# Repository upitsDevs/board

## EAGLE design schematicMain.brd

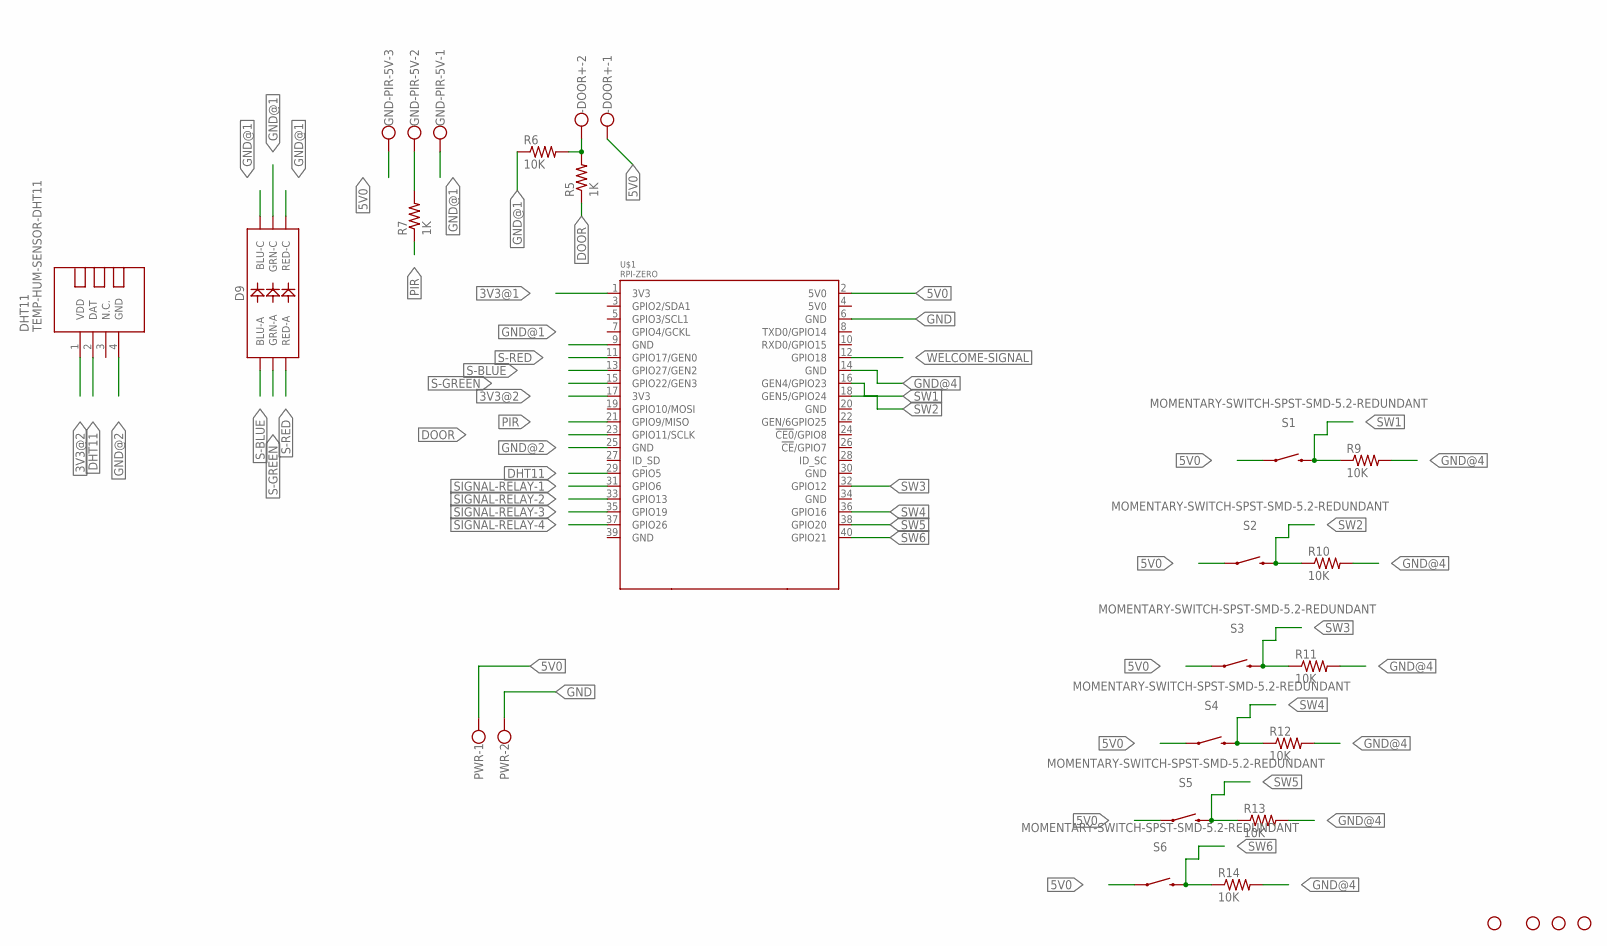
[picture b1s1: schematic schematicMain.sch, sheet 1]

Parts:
-DOOR+: W237-102
D9: RGB; LED-TRICOLOR-5050
DHT11: TEMP-HUM-SENSOR-DHT11
GND-PIR-5V: W237-103
H1, H2, H3, H4: STAND-OFFTIGHT; STAND-OFF-TIGHT
PWR: W237-102
R5, R7: 1K; M1206
R6, R9, R10, R11, R12, R13, R14: 10K; M1206
S1, S2, S3, S4, S5, S6: MOMENTARY-SWITCH-SPST-SMD-5.2-REDUNDANT; TACTILE_SWITCH_SMD_5.2MM
U$1: RPI-ZERO; RASPBERRYPI_BASTELSTUBE_V13_RASPI_BOARD_B+_FULL

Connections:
3V3@1: U$1.1 (3V3)
3V3@2: DHT11.1 (VDD), U$1.17 (3V3)
5V0: -DOOR+.1, GND-PIR-5V.3, PWR.1, S1.1, S1.2 (1), S2.1, S2.2 (1), S3.1, S3.2 (1), S4.1, S4.2 (1), S5.1, S5.2 (1), S6.1, S6.2 (1), U$1.2 (5V0); also elsewhere on the board
DHT11: DHT11.2 (DAT), U$1.29 (GPIO5)
DOOR: R5.1, U$1.23 (GPIO11/SCLK)
GND: PWR.2, U$1.6 (GND); also elsewhere on the board
GND@1: D9.4 (BLU-C), D9.5 (RED-C), D9.6 (GRN-C), GND-PIR-5V.1, R6.1, U$1.9 (GND)
GND@2: DHT11.4 (GND), U$1.25 (GND)
GND@4: R9.2, R10.2, R11.2, R12.2, R13.2, R14.2, U$1.14 (GND)
unnamed: GND-PIR-5V.2, R7.2
unnamed: -DOOR+.2, R5.2, R6.2
PIR: R7.1, U$1.21 (GPIO9/MISO)
S-BLUE: D9.3 (BLU-A), U$1.13 (GPIO27/GEN2)
S-GREEN: D9.1 (GRN-A), U$1.15 (GPIO22/GEN3)
S-RED: D9.2 (RED-A), U$1.11 (GPIO17/GEN0)
SIGNAL-RELAY-1: U$1.31 (GPIO6); also elsewhere on the board
SIGNAL-RELAY-2: U$1.33 (GPIO13); also elsewhere on the board
SIGNAL-RELAY-3: U$1.35 (GPIO19); also elsewhere on the board
SIGNAL-RELAY-4: U$1.37 (GPIO26); also elsewhere on the board
SW1: R9.1, S1.3 (2), S1.4 (2), U$1.16 (GEN4/GPIO23)
SW2: R10.1, S2.3 (2), S2.4 (2), U$1.18 (GEN5/GPIO24)
SW3: R11.1, S3.3 (2), S3.4 (2), U$1.32 (GPIO12)
SW4: R12.1, S4.3 (2), S4.4 (2), U$1.36 (GPIO16)
SW5: R13.1, S5.3 (2), S5.4 (2), U$1.38 (GPIO20)
SW6: R14.1, S6.3 (2), S6.4 (2), U$1.40 (GPIO21)
WELCOME-SIGNAL: U$1.12 (GPIO18); also elsewhere on the board

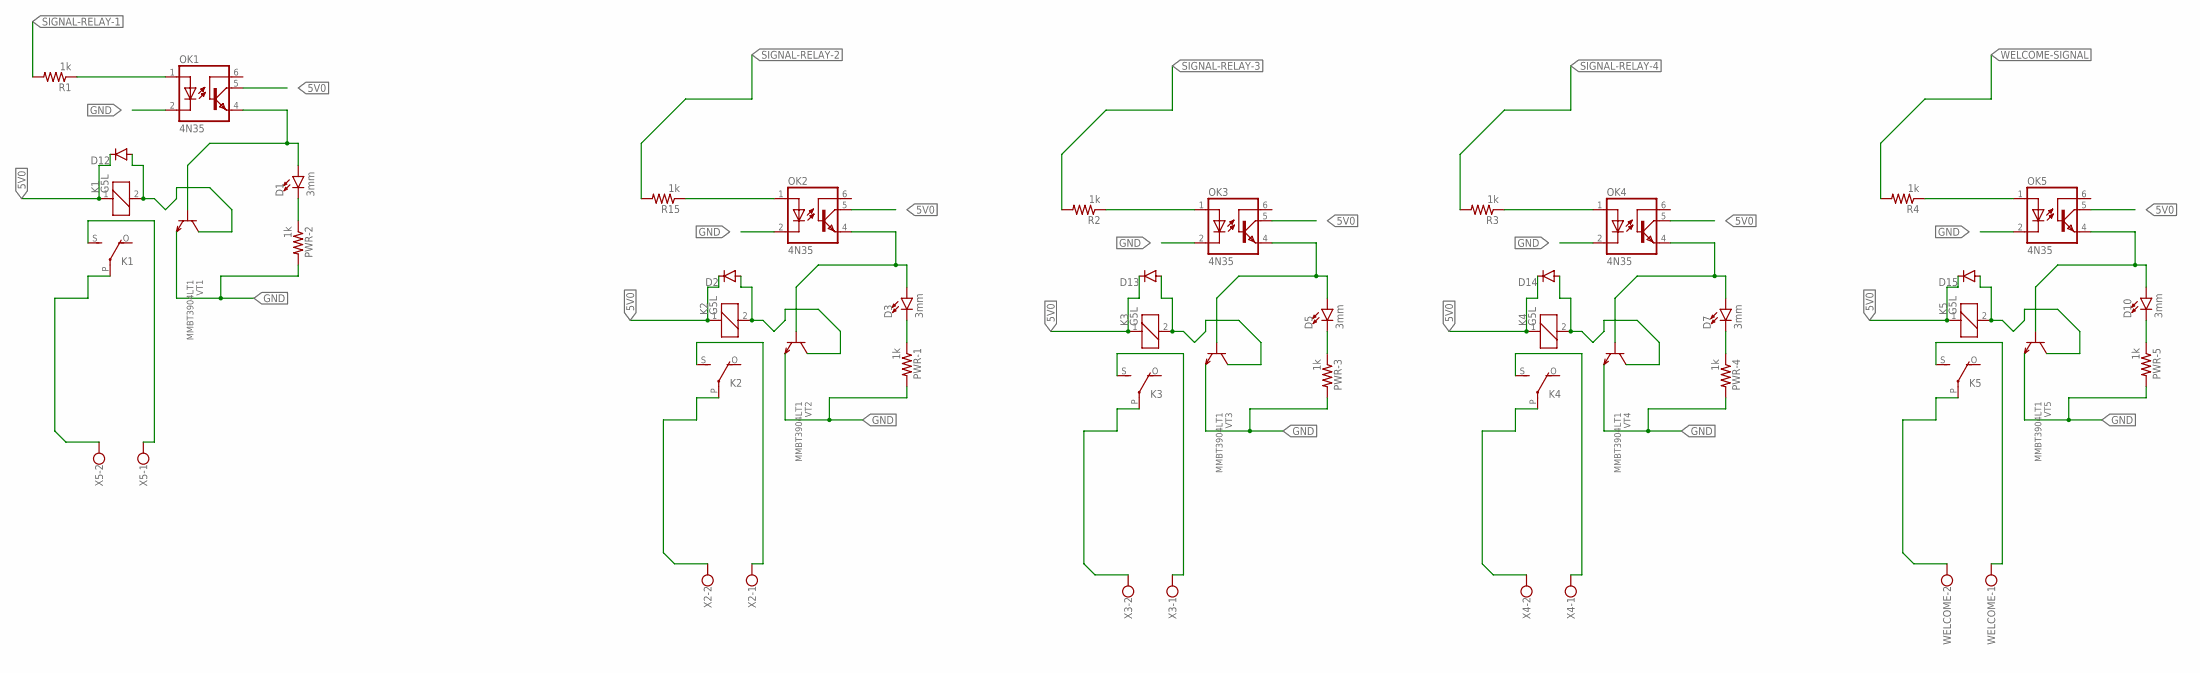
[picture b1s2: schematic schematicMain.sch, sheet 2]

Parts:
D1, D3, D5, D7, D10: 3mm; FKIT-LED-1206
D2, D12, D13, D14, D15: DIODE-SOD80C; SOD80C
K1, K2, K3, K4, K5: G5L; G5LE
OK1, OK2, OK3, OK4, OK5: 4N35; DIL06
PWR-1, PWR-2, PWR-3, PWR-4, PWR-5: 1k; M1206
R1, R2, R3, R4, R15: 1k; M1206
VT1, VT2, VT3, VT4, VT5: MMBT3904LT1; SOT23-BEC
WELCOME: W237-102
X2, X3, X4, X5: W237-102

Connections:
5V0: D2.C, D12.C, D13.C, D14.C, D15.C, K1.1, K2.1, K3.1, K4.1, K5.1, OK1.5 (COL), OK2.5 (COL), OK3.5 (COL), OK4.5 (COL), OK5.5 (COL); also elsewhere on the board
GND: OK1.2 (C), OK2.2 (C), OK3.2 (C), OK4.2 (C), OK5.2 (C), PWR-1.2, PWR-2.2, PWR-3.2, PWR-4.2, PWR-5.2, VT1.E, VT2.E, VT3.E, VT4.E, VT5.E; also elsewhere on the board
unnamed: K1.P, X5.2
unnamed: K1.S, X5.1
unnamed: K2.P, X2.2
unnamed: D1.A, OK1.4 (EMI), VT1.B
unnamed: D12.A, K1.2, VT1.C
unnamed: K5.P, WELCOME.2
unnamed: OK1.1 (A), R1.1
unnamed: K2.S, X2.1
unnamed: K5.S, WELCOME.1
unnamed: OK2.1 (A), R15.1
unnamed: D2.A, K2.2, VT2.C
unnamed: K3.P, X3.2
unnamed: K3.S, X3.1
unnamed: OK3.1 (A), R2.1
unnamed: OK5.1 (A), R4.1
unnamed: D13.A, K3.2, VT3.C
unnamed: D5.A, OK3.4 (EMI), VT3.B
unnamed: D5.C, PWR-3.1
unnamed: D15.A, K5.2, VT5.C
unnamed: K4.P, X4.2
unnamed: K4.S, X4.1
unnamed: D10.A, OK5.4 (EMI), VT5.B
unnamed: OK4.1 (A), R3.1
unnamed: D14.A, K4.2, VT4.C
unnamed: D7.A, OK4.4 (EMI), VT4.B
unnamed: D3.A, OK2.4 (EMI), VT2.B
unnamed: D1.C, PWR-2.1
unnamed: D3.C, PWR-1.1
unnamed: D7.C, PWR-4.1
unnamed: D10.C, PWR-5.1
SIGNAL-RELAY-1: R1.2; also elsewhere on the board
SIGNAL-RELAY-2: R15.2; also elsewhere on the board
SIGNAL-RELAY-3: R2.2; also elsewhere on the board
SIGNAL-RELAY-4: R3.2; also elsewhere on the board
WELCOME-SIGNAL: R4.2; also elsewhere on the board

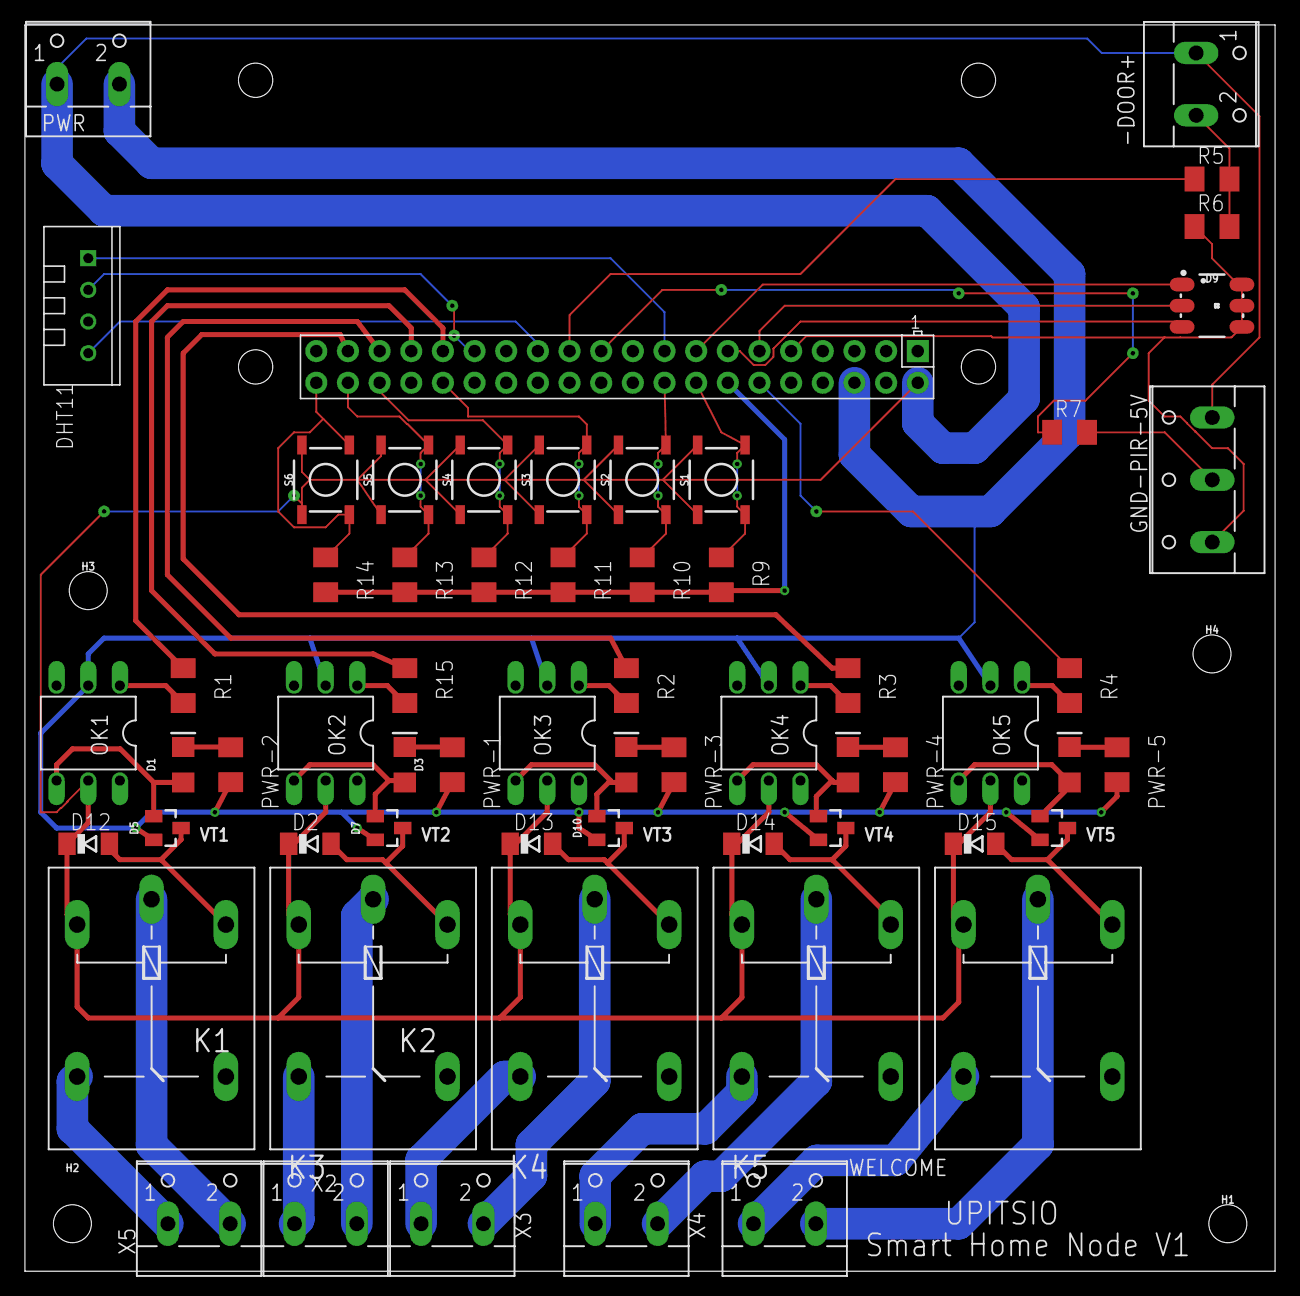
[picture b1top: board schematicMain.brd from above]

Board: 2 copper layers, 100.3 x 100.0 mm, 65 parts (0 on the bottom side), 55 nets.

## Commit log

2018-11-21 initial version
2018-11-21 Read me
2018-11-21 Updated Relay modules
2018-11-23 update 23-11-2018
2018-11-23 Pcb design finished
2018-11-24 update 24-11-2018 6:38AM

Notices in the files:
parts and their libraries:
SparkFun-LED: Licensing: Creative Commons ShareAlike 4.0 International - https://creativecommons.org/licenses/by-sa/4.0
diy-modules: Released under the Creative Commons Attribution 4.0 International License: http://creativecommons.org/licenses/by/4.0
